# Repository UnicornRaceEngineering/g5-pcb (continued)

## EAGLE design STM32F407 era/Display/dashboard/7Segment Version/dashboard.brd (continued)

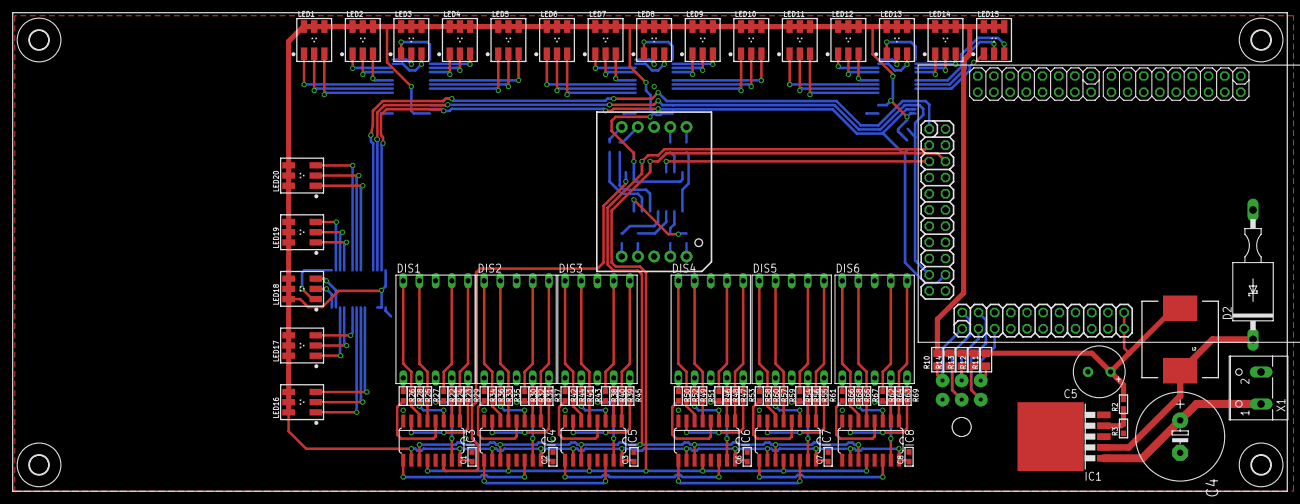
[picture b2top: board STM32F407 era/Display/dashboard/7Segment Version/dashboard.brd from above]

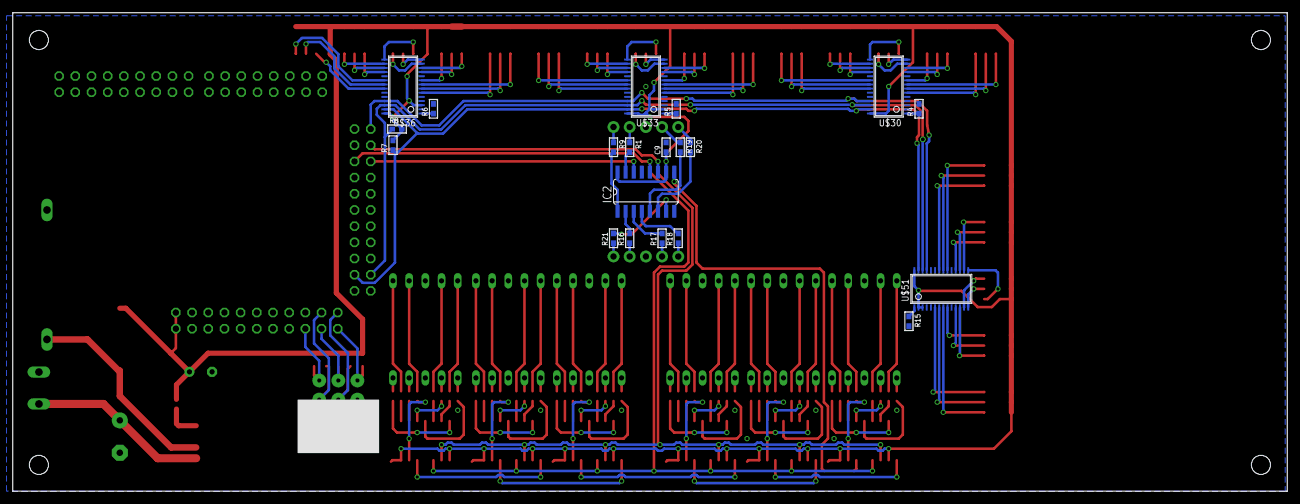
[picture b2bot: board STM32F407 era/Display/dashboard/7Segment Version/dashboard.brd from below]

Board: 2 copper layers, 200.0 x 75.1 mm, 126 parts (21 on the bottom side), 198 nets.

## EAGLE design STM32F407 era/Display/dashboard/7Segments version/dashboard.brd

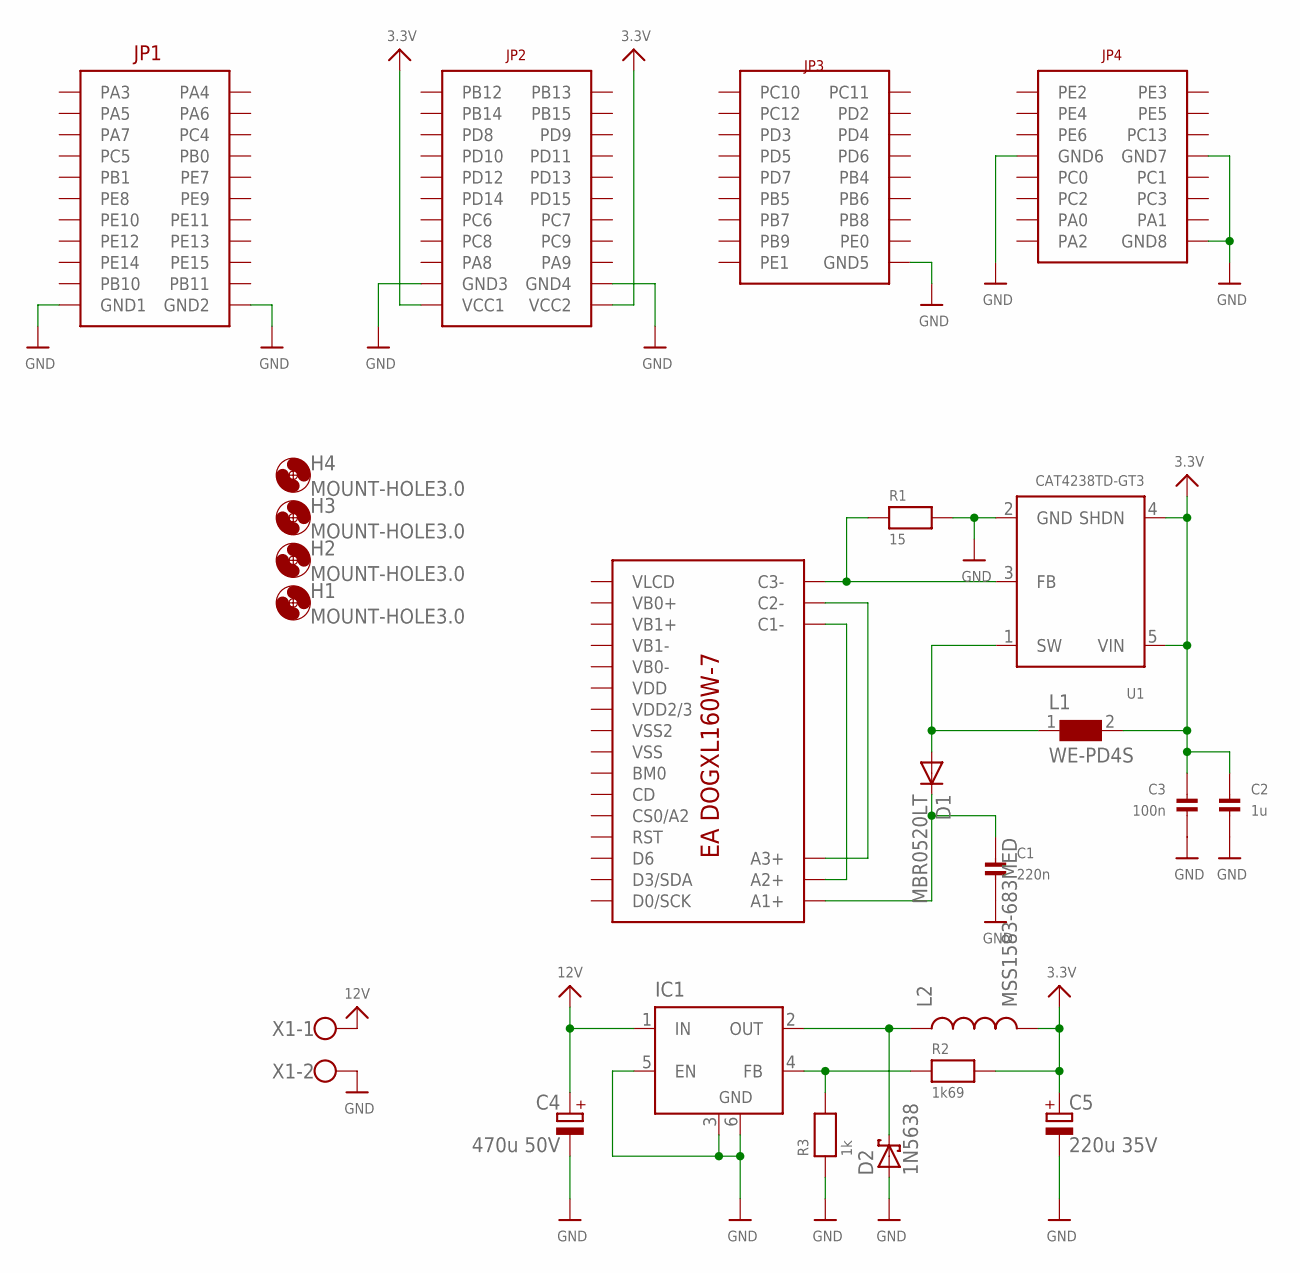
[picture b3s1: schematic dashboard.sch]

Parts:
C1: 220n; _0805
C2: 1u; _0805
C3: 100n; _0603
C4: 470u 50V; E5-13
C5: 220u 35V; E3,5-8
D1: MBR0520LT; SOD123
D2: 1N5638; DO13M
H1, H2, H3, H4: MOUNT-HOLE3.0; 3,0
IC1: LM2596S; TO263-5
L1: WE-PD4S; S
L2: MSS1583-683MED; CDRH125
R1: 15; _0603
R2: 1k69; _0603
R3: 1k; _0603
U1: CAT4238TD-GT3; SOT23-5
U$1: CPU-BOARD; CPU-BOARD-JP1
U$10: EA-DOGXL160W-7
X1: W237-102

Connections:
3.3V: C2.1, C3.1, C5.+, L1.2, L2.2, R2.2, U1.4 (SHDN), U1.5 (VIN), U$1.P$43 (VCC1), U$1.P$44 (VCC2)
12V: C4.+, IC1.1 (IN), X1.1
GND: C1.2, C2.2, C3.2, C4.-, C5.-, D2.A, IC1.3 (GND), IC1.5 (EN), IC1.6 (GND), R1.2, R3.1, U1.2 (GND), U$1.P$21 (GND1), U$1.P$22 (GND2), U$1.P$41 (GND3), U$1.P$42 (GND4), U$1.P$62 (GND5), U$1.P$69 (GND6), U$1.P$70 (GND7), U$1.P$78 (GND8), X1.2
unnamed: U$10.P$2 (A2+), U$10.P$14 (C1-)
unnamed: U$10.P$3 (A3+), U$10.P$15 (C2-)
unnamed: R1.1, U1.3 (FB), U$10.P$16 (C3-)
unnamed: C1.1, D1.C, U$10.P$1 (A1+)
unnamed: D1.A, L1.1, U1.1 (SW)
unnamed: IC1.4 (FB), R2.1, R3.2
unnamed: D2.C, IC1.2 (OUT), L2.1

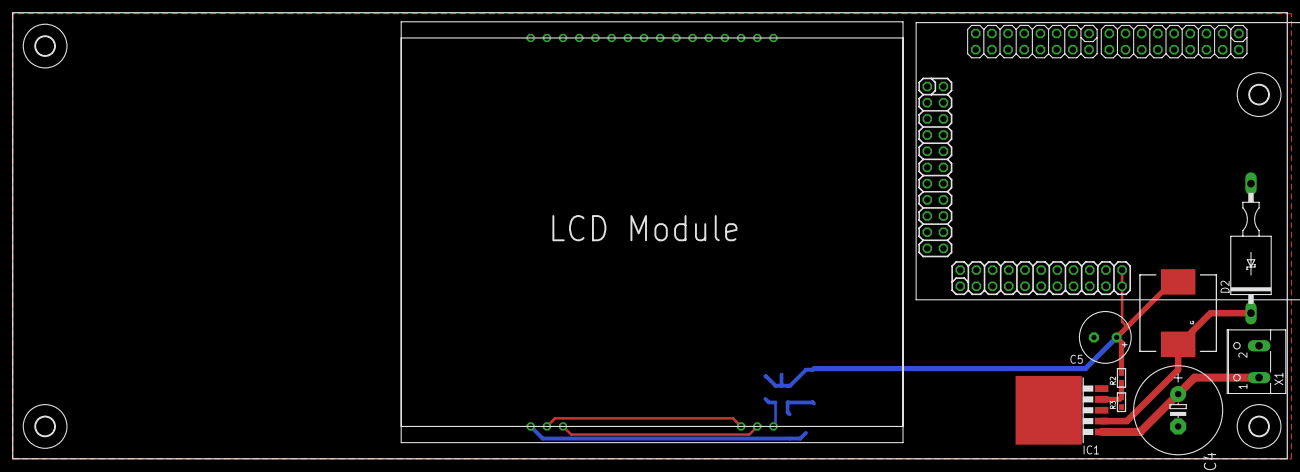
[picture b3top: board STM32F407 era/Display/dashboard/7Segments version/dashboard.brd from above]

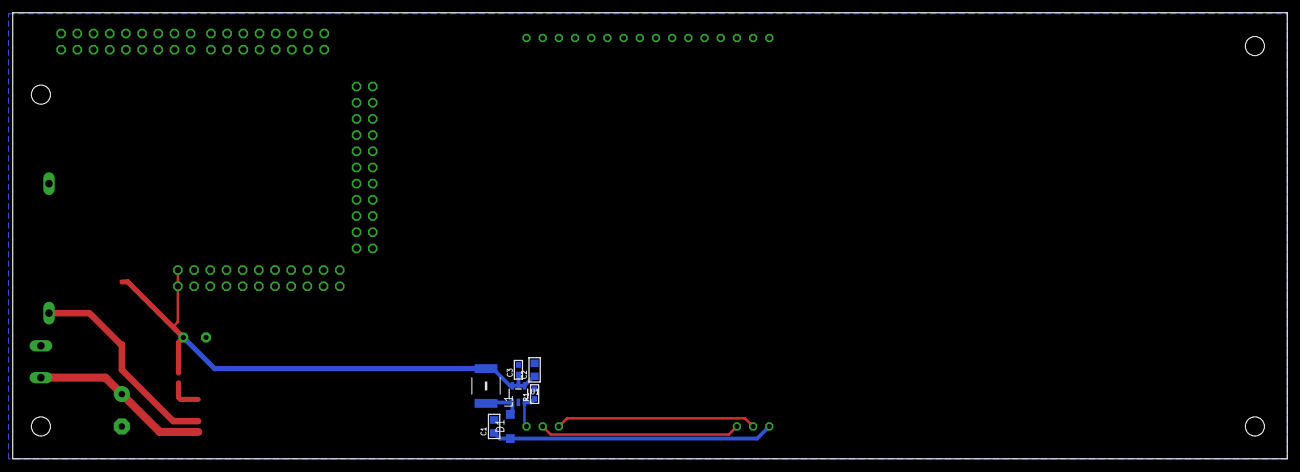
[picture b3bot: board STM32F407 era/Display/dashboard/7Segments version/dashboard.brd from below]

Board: 2 copper layers, 200.0 x 70.0 mm, 21 parts (7 on the bottom side), 10 nets.

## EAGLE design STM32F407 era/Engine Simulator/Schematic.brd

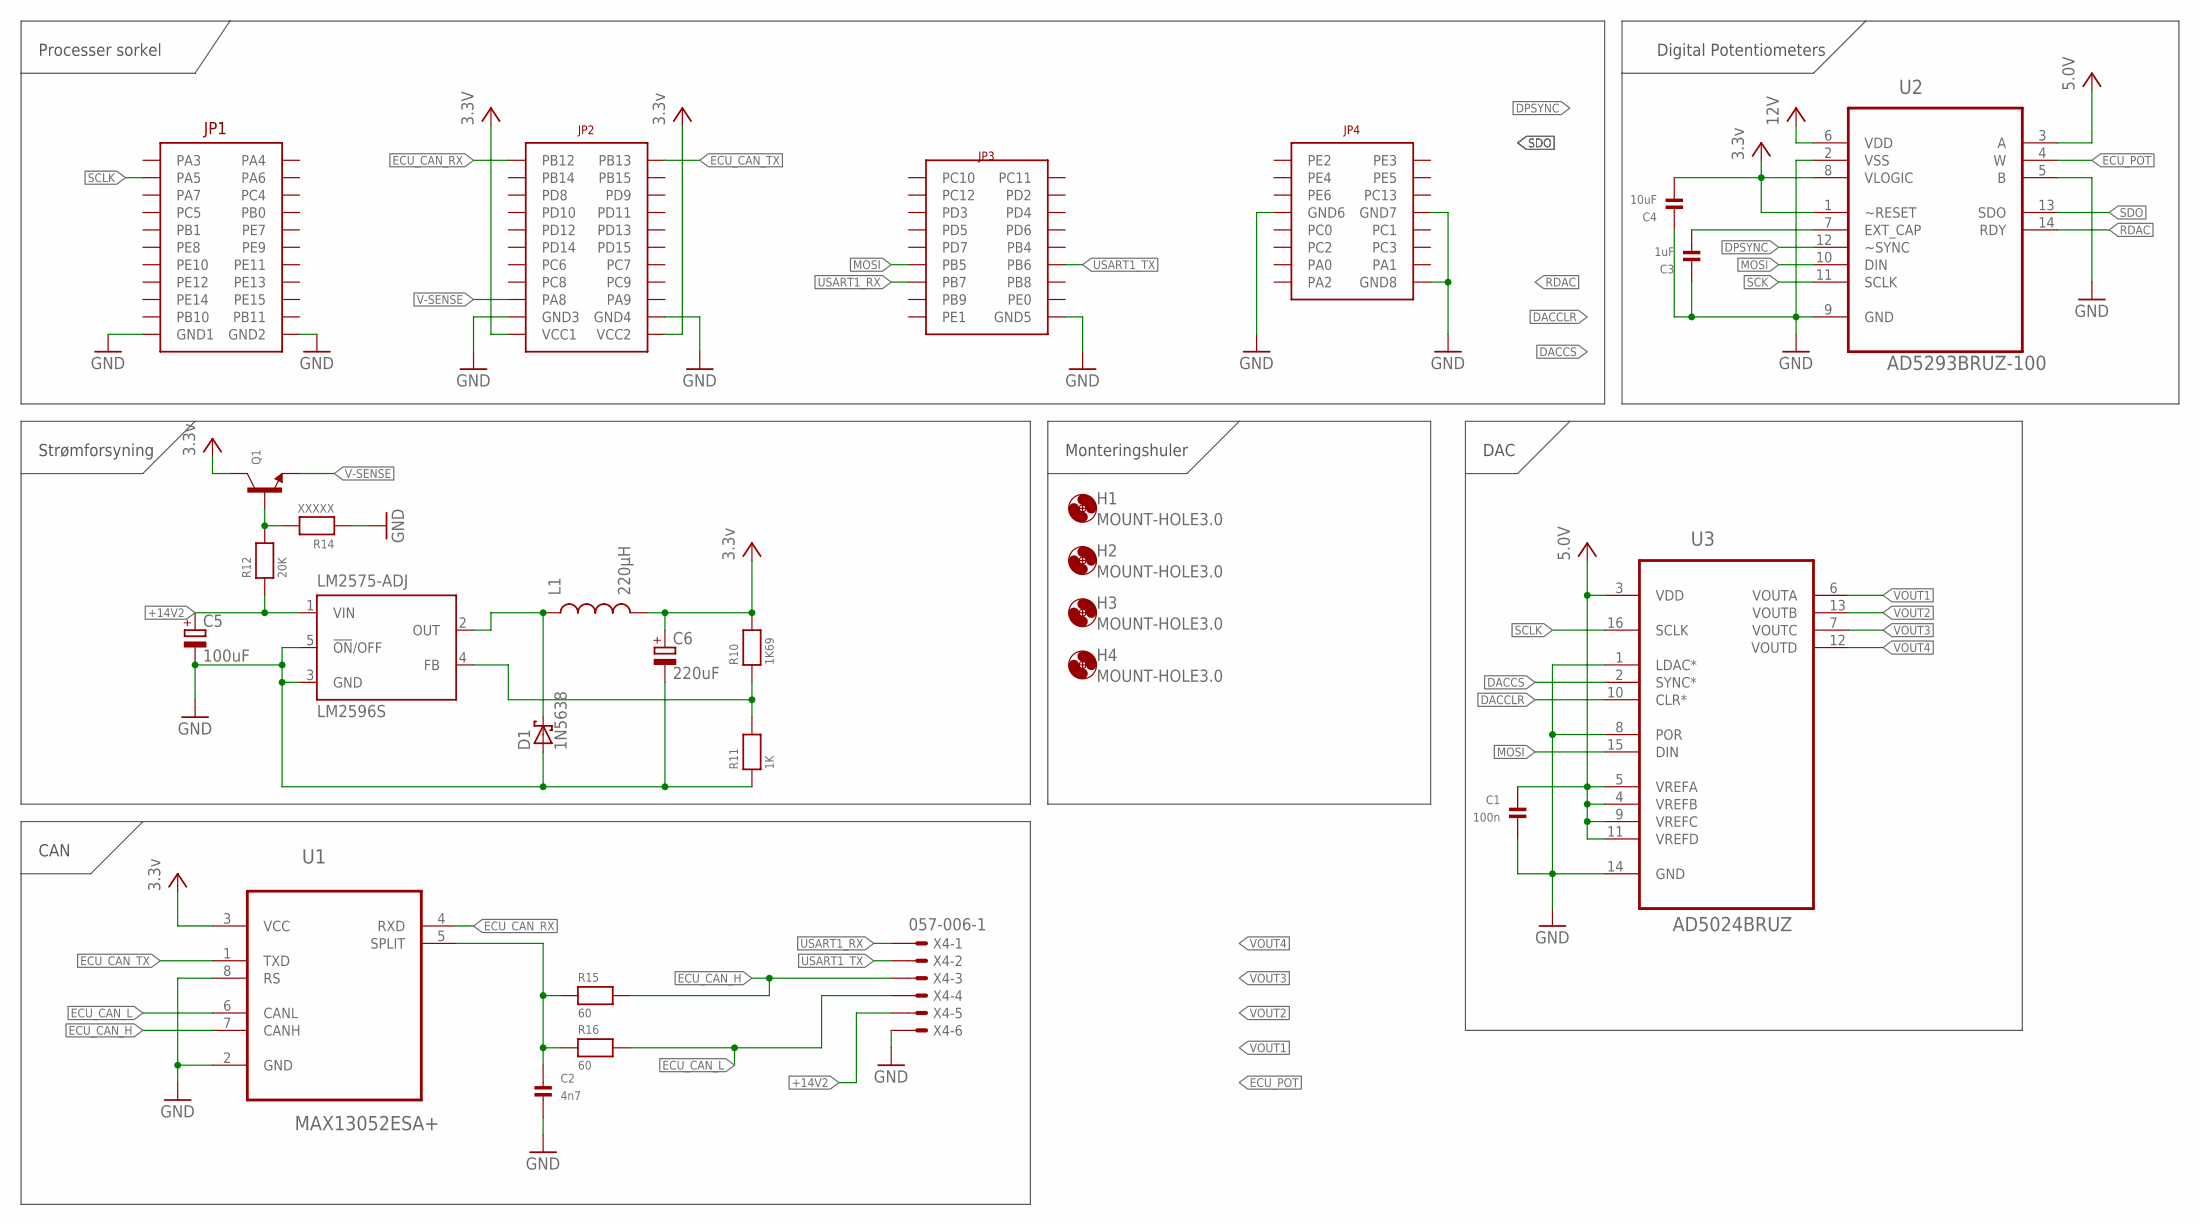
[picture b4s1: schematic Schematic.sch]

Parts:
C1: 100n; _0603
C2: 4n7; 0603
C3: 1uF; 0603
C4: 10uF; 0603
C5: 100uF; E15-5
C6: 220uF; E15-5
D1: 1N5638; DO13M
H1, H2, H3, H4: MOUNT-HOLE3.0; 3,0
L1: 220µH; CDRH125
LM2575-ADJ: LM2596S; TO263-5
Q1: TRANSISTOR_NPNWIDE; SOT23-WIDE
R10: 1K69; _0603
R11: 1K; _0603
R12: 20K; _0603
R14: XXXXX; _0603
R15, R16: 60; _0603
U1: MAX13052ESA+; SOIC127P600X175-8N
U2: AD5293BRUZ-100; SOP65P640X120-14N
U3: AD5024BRUZ; SOP65P640X120-16N
U$1: CPU-BOARD; CPU-BOARD-JP1
X4: 057-006-1

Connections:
+14V2: C5.+, LM2575-ADJ.1 (VIN), R12.1, X4.5
DACCLR: U3.10 (CLR*)
DACCS: U3.2 (SYNC*)
DPSYNC: U2.12 (~SYNC)
ECU_CAN_H: R15.2, U1.7 (CANH), X4.3
ECU_CAN_L: R16.2, U1.6 (CANL), X4.4
ECU_CAN_RX: U1.4 (RXD), U$1.P$23 (PB12)
ECU_CAN_TX: U1.1 (TXD), U$1.P$24 (PB13)
ECU_POT: U2.4 (W)
GND: C1.2, C2.2, C3.1, C4.1, C5.-, C6.-, D1.A, LM2575-ADJ.3 (GND), LM2575-ADJ.5 (!ON!/OFF), R11.1, R14.1, U1.2 (GND), U1.8 (RS), U2.2 (VSS), U2.5 (B), U2.9 (GND), U3.1 (LDAC*), U3.8 (POR), U3.14 (GND), U$1.P$20 (GND2), U$1.P$41 (GND3), U$1.P$42 (GND4), U$1.P$62 (GND5), U$1.P$69 (GND6), U$1.P$70 (GND7), U$1.P$78 (GND8), X4.6
MOSI: U2.10 (DIN), U3.15 (DIN), U$1.P$55 (PB5)
unnamed: C3.2, U2.7 (EXT_CAP)
unnamed: D1.C, L1.1, LM2575-ADJ.2 (OUT)
unnamed: LM2575-ADJ.4 (FB), R10.1, R11.2
unnamed: Q1.1 (B), R12.2, R14.2
unnamed: C2.1, R15.1, R16.1, U1.5 (SPLIT)
PE: U$1.P$19 (GND1)
RDAC: U2.14 (RDY)
SCK: U2.11 (SCLK)
SCLK: U3.16 (SCLK), U$1.P$3 (PA5)
SDO: U2.13 (SDO)
USART1_RX: U$1.P$57 (PB7), X4.1
USART1_TX: U$1.P$56 (PB6), X4.2
V-SENSE: Q1.2 (E), U$1.P$39 (PA8)
VCC: C1.1, C4.2, C6.+, L1.2, Q1.3 (C), R10.2, U1.3 (VCC), U2.1 (~RESET), U2.3 (A), U2.6 (VDD), U2.8 (VLOGIC), U3.3 (VDD), U3.4 (VREFB), U3.5 (VREFA), U3.9 (VREFC), U3.11 (VREFD), U$1.P$43 (VCC1), U$1.P$44 (VCC2)
VOUT1: U3.6 (VOUTA)
VOUT2: U3.13 (VOUTB)
VOUT3: U3.7 (VOUTC)
VOUT4: U3.12 (VOUTD)

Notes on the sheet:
CAN
Strømforsyning
Processer sorkel
Monteringshuler
Digital Potentiometers
DAC

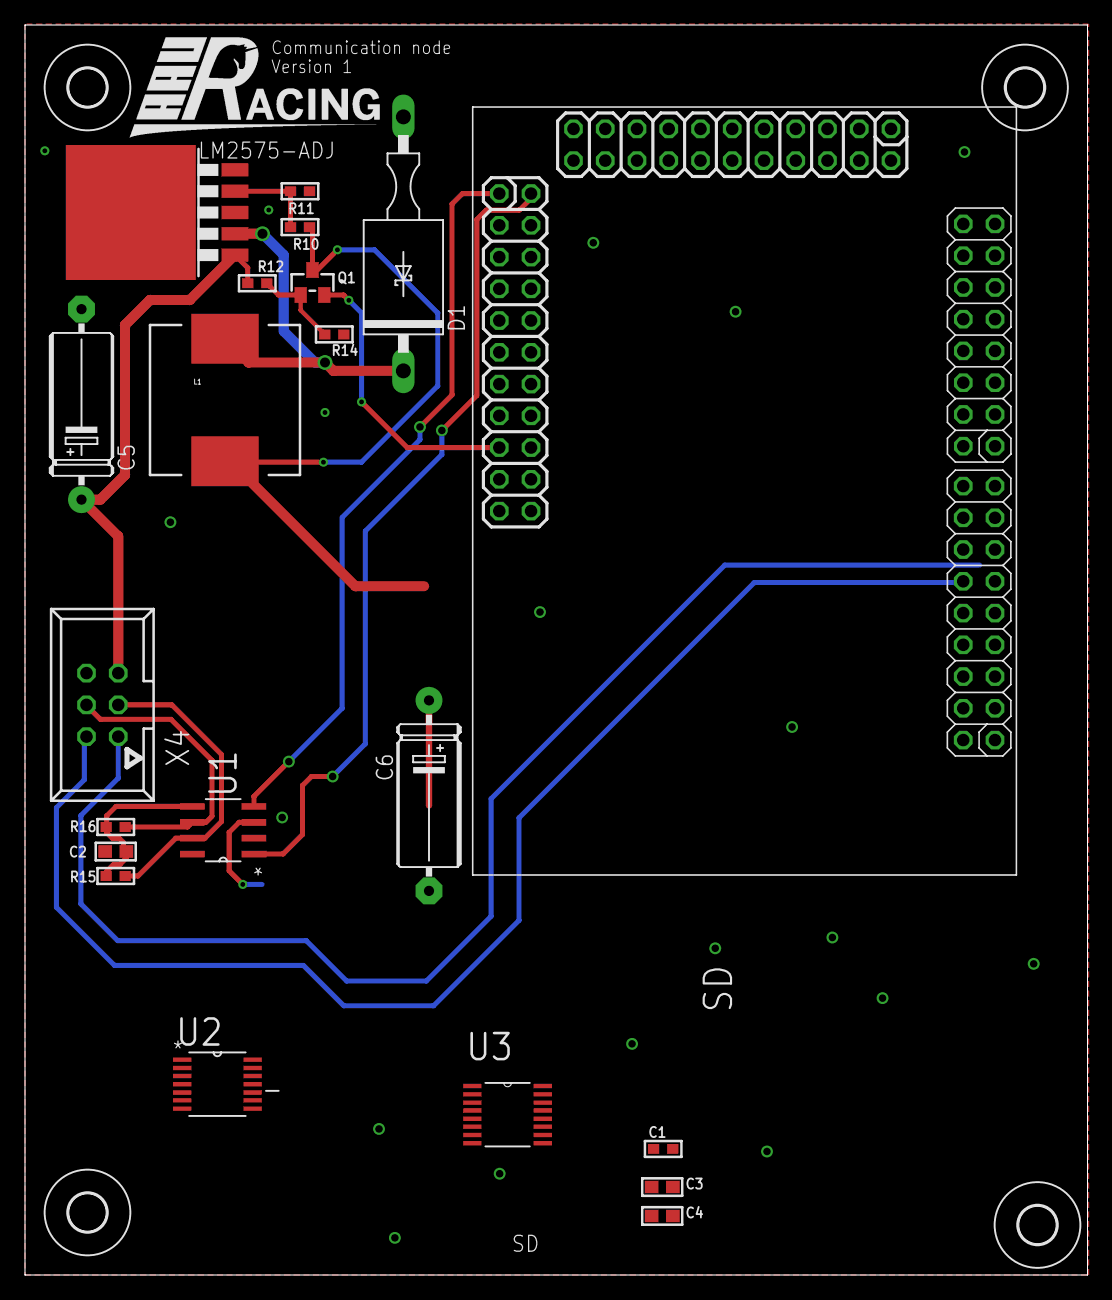
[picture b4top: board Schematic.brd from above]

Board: 2 copper layers, 85.0 x 100.0 mm, 25 parts (0 on the bottom side), 17 nets.

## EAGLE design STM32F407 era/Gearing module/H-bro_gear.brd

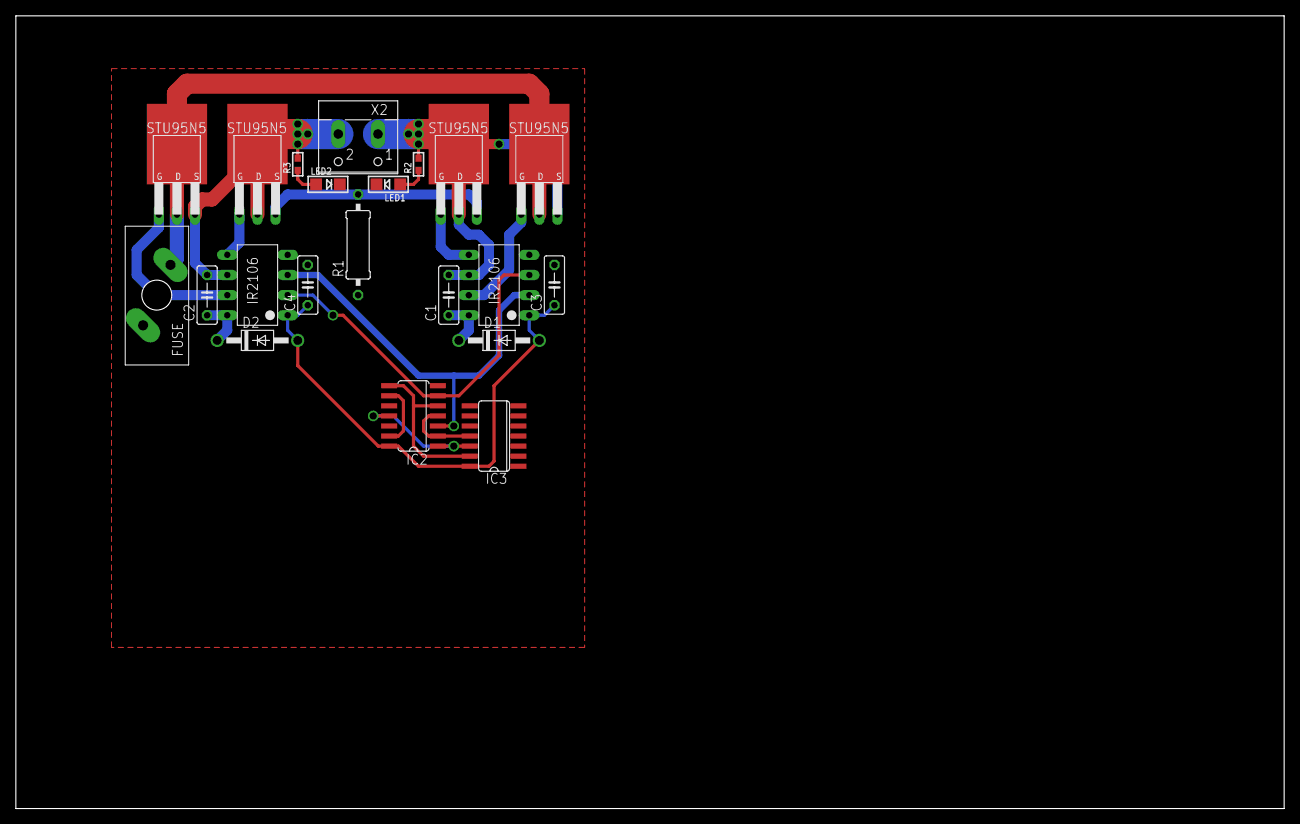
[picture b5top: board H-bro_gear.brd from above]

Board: 2 copper layers, 160.0 x 100.0 mm, 21 parts (0 on the bottom side), 20 nets.

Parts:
C1, C2, C3, C4: C050-025X075
D1, D2: 1N4004; DO41-10
IC2: 74AC08D; SO14
IC3: 4070D; SO14
LED1, LED2: CHIPLED_1206
R1: 0309/12
R2, R3: _0603
U$1, U$2: IR2106
U$3, U$4, U$5, U$6: STU95N5
U$7: LITTE_FUSE; LITTE_FUSE_PAC
X2: W237-102

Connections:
+5V: C3.1, C4.1, D1.A, D2.A, IC2.14, IC3.14, U$1.VCC, U$2.VCC
DIR0: IC2.3, U$1.HIN, U$2.LIN
DIR1: IC2.6, U$1.LIN, U$2.HIN
GND: C3.2, C4.2, IC2.7, IC3.7, LED1.C, LED2.C, R1.1, U$1.COM, U$2.COM
unnamed: U$1.HO, U$3.G
unnamed: U$1.LO, U$4.G
unnamed: U$2.HO, U$6.G
unnamed: U$2.LO, U$5.G
unnamed: C1.2, R2.2, U$1.VS, U$3.S, U$4.D, U$4.TAB, X2.1
unnamed: C2.2, R3.2, U$2.VS, U$5.D, U$5.TAB, U$6.S, X2.2
unnamed: U$3.D, U$3.TAB, U$6.D, U$6.TAB, U$7.P$2
unnamed: C1.1, D1.C, U$1.VB
unnamed: R1.2, U$4.S, U$5.S
unnamed: C2.1, D2.C, U$2.VB
unnamed: IC2.2, IC2.4, IC3.11
unnamed: IC2.1, IC2.11, IC3.12
unnamed: IC2.5, IC2.8, IC3.13
unnamed: LED1.A, R2.1
unnamed: LED2.A, R3.1
OPC: IC2.9, IC2.13
